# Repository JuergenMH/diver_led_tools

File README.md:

# diver_led_tools
This repository contains two projects or units.

The first one is a LED "Diver marker" and the second one is "Diver flasher".
Both devices are tools for scuba drivers.
It shares some ressources, this was the reason to put them into one repository.

## Folders
    2D drawings:            brainstorming folder with ideas how to create possible water proofed housings for the diver marker/flasher.
    documents:              different documents regarding both units.
    Firmware_diver_flasher: currently a copy of an older project which will be the base for the new software
    FIrmware_diver_marker:  ditto
    Pcb_Diver_Marker:       Eagle (7.6) PCB for this unit
    Pcb_Diver_Flasher:      KiCAD (8.0) PCB for this unit
    SKEDD-PIC-Cable:        KiCAD (8.0) schematic for the connection cable PICKIT <> PCB for program and debug purposes

## Current state (14.12.2024)
The folder structures and content are still under construction!

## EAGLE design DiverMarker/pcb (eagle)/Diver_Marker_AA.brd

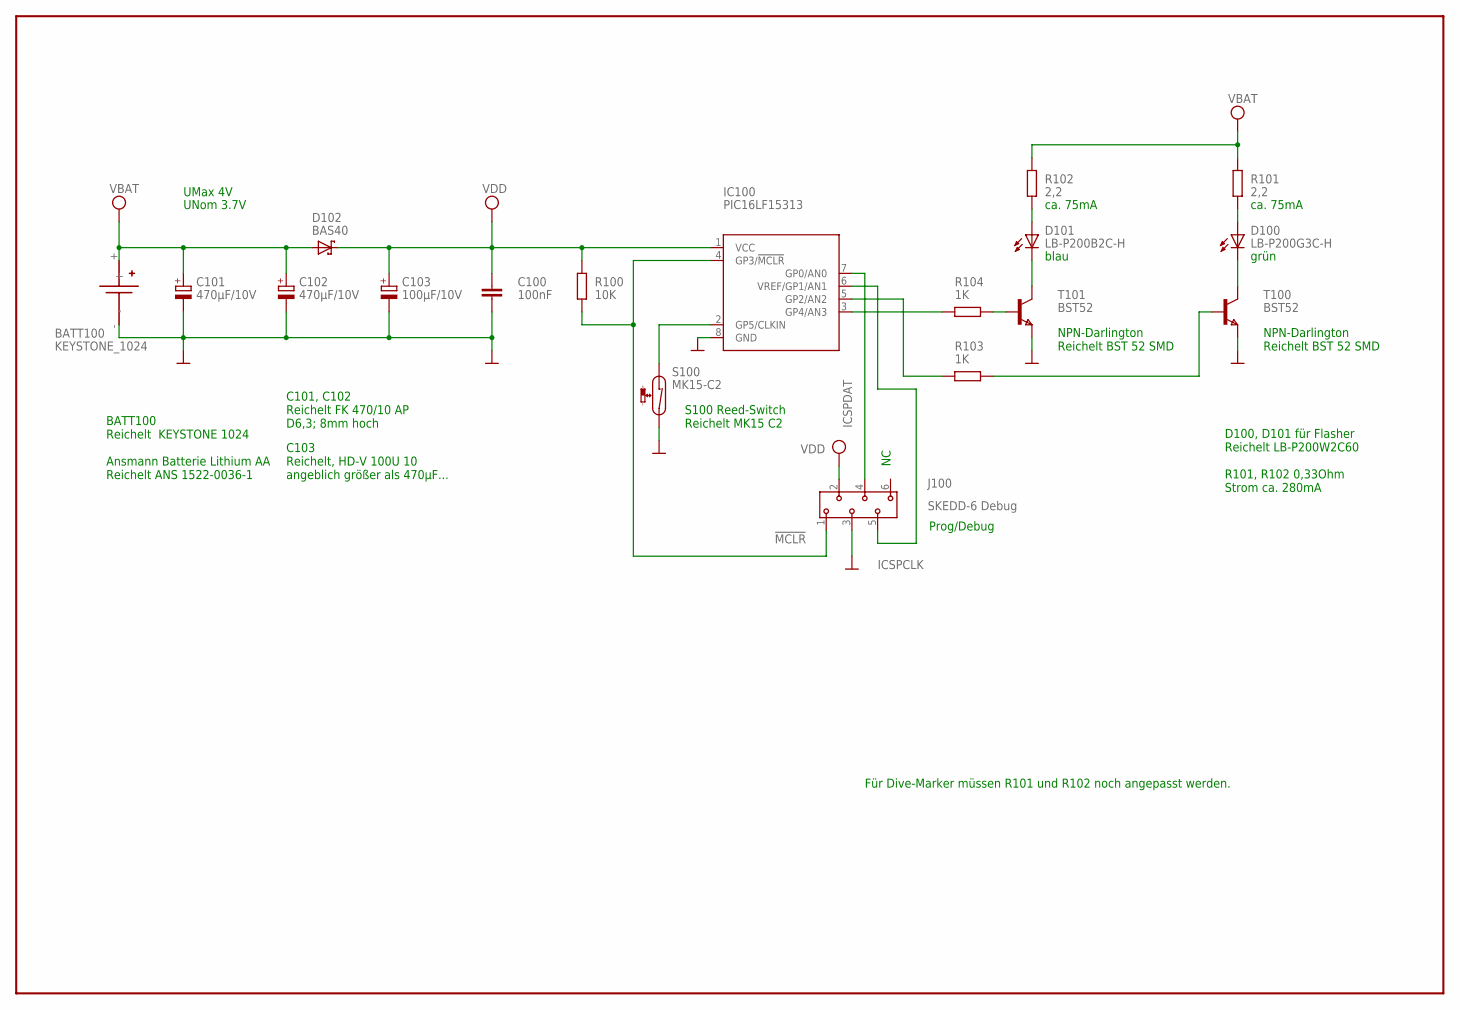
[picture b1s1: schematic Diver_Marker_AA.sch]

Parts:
BATT100: KEYSTONE_1024; KEYSTONE_1024_AA_SMD
C100: 100nF; C0805
C101, C102: 470µF/10V; 153CLV-0605
C103: 100µF/10V; 153CLV-0605
D100: LB-P200G3C-H; Z-POWER-LED-PCB-TYPE
D101: LB-P200B2C-H; Z-POWER-LED-PCB-TYPE
D102: BAS40; SOT23
IC100: PIC16LF15313; SO-08
J100: SKEDD-6 Debug; 490107670612_DEBUGGING
R100: 10K; R0805
R101, R102: 2,2; R0805
R103, R104: 1K; R0805
S100: MK15-C2; MK15
T100, T101: BST52; SOT89

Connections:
!MCLR: IC100.4 (GP3/!MCLR), J100.1, R100.1
B0: R103.1, T100.1 (B)
B1: R104.1, T101.1 (B)
GND: BATT100.-, C100.2, C101.-, C102.-, C103.-, IC100.8 (GND), J100.3, S100.2, T100.3 (E), T101.3 (E)
ICSPCLK: IC100.6 (VREF/GP1/AN1), J100.5
ICSPDAT: IC100.7 (GP0/AN0), J100.4
L0: D100.C, T100.2 (C), T100.2@1 (C)
L1: D101.C, T101.2 (C), T101.2@1 (C)
unnamed: IC100.3 (GP4/AN3), R104.2
unnamed: D101.A, R102.1
unnamed: D100.A, R101.1
OUT0: IC100.5 (GP2/AN2), R103.2
REED: IC100.2 (GP5/CLKIN), S100.1
VCC: BATT100.+, C101.+, C102.+, D102.1 (A), R101.2, R102.2
VDD: C100.1, C103.+, D102.3 (C), IC100.1 (VCC), J100.2, R100.2

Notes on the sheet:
UNom 3.7V
UMax 4V
ca. 75mA
Prog/Debug
S100 Reed-Switch Reichelt MK15 C2
C101, C102 Reichelt FK 470/10 AP D6,3; 8mm hoch
C103 Reichelt, HD-V 100U 10 angeblich größer als 470µF...
Für Dive-Marker müssen R101 und R102 noch angepasst werden.
BATT100 Reichelt KEYSTONE 1024 Ansmann Batterie Lithium AA Reichelt ANS 1522-0036-1
D100, D101 für Flasher Reichelt LB-P200W2C60 R101, R102 0,33Ohm Strom ca. 280mA
NPN-Darlington Reichelt BST 52 SMD
blau
grün

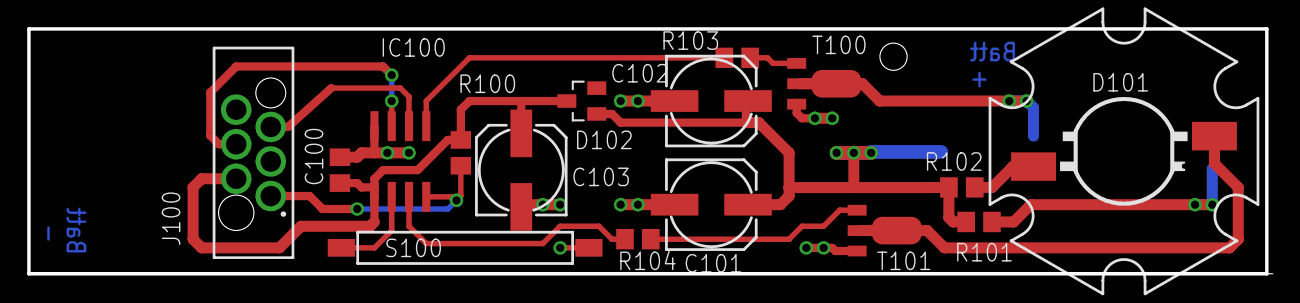
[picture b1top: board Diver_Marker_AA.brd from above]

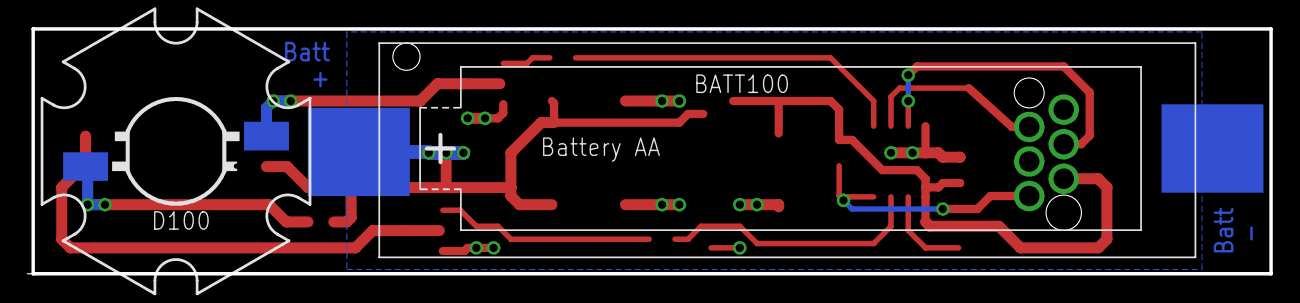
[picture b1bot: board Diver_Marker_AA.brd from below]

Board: 2 copper layers, 91.3 x 18.0 mm, 18 parts (2 on the bottom side), 15 nets.

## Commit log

2024-12-14 Initial commit to add existing files and folders to the empty repository
2024-12-14 Update README.md
    Readme changed for test purposes only.
2024-12-16 SW adapted for new hardware
    First version for new hardware, can be compiled but it is not tested yet.
2024-12-18 Inter mediate check in
    HW: is working; LED current propably to low
    SW: Basic functions are working.
    System enters sleep; wakeup not working
    Switch handling for manual on/off not implemented
2024-12-18 Sleep / Wakeup now working
    Auto power off still set to one minute (for easy debugging)
    Next todo: Implement user power off
2024-12-18 First working version of the software
    Reed switch handling implemented
    - Reed activated = flasher running
    - Reed deactivated = flasher enter sleep
    If flasher is activated for 90 minutes it will enter auto power off.
2024-12-26 Information regaring inductor and diode added
2024-12-26 Document with issues first prototype added. Word / German
2024-12-26 Intermediate check in
2025-01-03 Simulation folder added
    A simulation for a more powerful booster circuit was added.
2025-01-06 New datasheets and simulations added. Target is to improve the power of the booster circuit of the diver flasher.
2025-01-12 backups removed
2025-01-12 ignore fie added.
2025-01-15 again; zip files removed
2025-01-15 Started with version 1.1 of the dive flasher PCB. 1.0 => old too weak booster 1.1 => new hopefully more powerful booster
2025-02-09 New simulation added.
2025-02-09 Start with next version "home brew" boost converter
2025-02-19 Firmware folder diver flasher renamed Software new generated with melody framework
2025-02-21 New FW structure added for diver marker No functions implemented yet
2025-02-21 New structure for the diver marker. Ready: Pulse generation Tested on desk only: basic I regulation of pulse width Application: 50ms on, 950ms off, not power up/down yet
2025-02-21 PCB diver flasher restored
2025-03-03 Update to KiCAD 9
2025-03-03 main.c is working now
2025-03-09 Old PC (v1) removed Latest changes for current schematic routed. Almost ready DRC outstanding.
2025-03-09 Project reorganised: - Outdate and backup files removed - diver flasher and diver marker moved to separate folders
2025-03-28 New pcb design with KiCAD 9 started. Old eagle design moved to archive folder.
2025-04-04 DRC errors removed, finished
2025-04-07 Backup files removed
2025-04-09 Routing PCB diver marker started; almost ready but a least of open drc errors.
2025-04-09 pcb finished errors almost removed
2025-04-10 Unused datasheets removed Keystone 1024 tested but not used because of space requirements. Still THT version used on board.
2025-04-10 Updates on Backup folder
2025-04-11 Two additional inductor types from Würth added.
2025-04-11 Distributors for all componentes added.
2025-04-12 Working on BON
2025-04-14 Working on PCB documentation
2025-04-27 Component placement optimisation. No functional changes
2025-04-27 PCB sizes added on layer user 1
2025-04-27 Production data with JLCPCB plugin generated
2025-05-04 Side view of the PCB on measurement layer added.
2025-05-04 Side View on Measurment layer added
2025-05-07 No functional changes
2025-05-07 Setup firmware within MCC, coding startet; timer not running correct yet.
2025-05-07 PCB informations added
2025-05-09 Work on firmware / HW - activate sleep (not finished yet) - To Do list for next version PCB added
2025-05-09 Work on HW and SW
    - To Do list for next version of pcb
    - Start coding firmware (currently issue with PA.5)
2025-05-09 PortA.5 issue fixed (External oszillator was not disabled; Clock setup)
2025-05-09 Working on sleep mode Currently no wakeup
2025-05-10 Sleep and wakeup are working now. On time is minimum 3 cycles.
    ToDo: Check current consumption to validate HW and SW for battery life time.
2025-05-10 Sleep and wakeup is working now. Minimum on cycles is 3 cycles
    => at this moment same user logic as diver flasher!
    Next steps:
    - Implement 2 or 3 different lightning levels (SW)
    - Validate current consumption to validate HW and SW
2025-05-10 Ruhestrom hinzugefügt (50µA)
2025-05-10 Änderung durch MPLab
2025-05-10 Minor changes: - LED blue replaced by red one (curret is on blue too low) - LED resistors changed from 2.2Ohm to 1Ohm - quiescent current added (about 25µA)
2025-05-10 Two power modes added.
    Cycle on, off, on agwain within the first min cycle switches to high power
2025-05-11 Intensity method changed from time (not good) to a software PWM (much better).
2025-05-12 Timing und current check. No functional changes
2025-05-18 Platineneigenschaften und Lagenaufbau au PCB-Sheet hinzugefügt.
2025-05-18 Materialrecherche Amazon hinzugefügt.
2025-05-24 Weitere Daten zu Gehäuseinformationen hinzugefügt
2025-05-24 Global .ignore file added Empty folders with dummy content to get structure into repo.
2025-05-24 Local .gitignore by project global replaced.
2025-05-24 production zip added
2025-05-24 Document folder added.
2025-05-24 - Archiv removed - Document folder added
2025-05-24 Battery calculation update
2025-05-31 Drawing of bottom housing part added.
2025-05-31 Two more accu datasheets.
2025-05-31 Rohrbodenzeichnung vervollständigt.
2025-06-28 Datasheet update
2025-06-28 Calculation update regarding last measurements
2025-06-28 Table with current measurements added.
2025-06-30 Mechanical BOM added
2025-07-07 Adjusted CPU frequency from 32MHz to 1Mhz.

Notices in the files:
parts and their libraries:
Eagle_WR-WST: Copyright: Würth Elektronik
